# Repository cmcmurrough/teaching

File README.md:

teaching
========

Repository containing files related to CSE curriculum

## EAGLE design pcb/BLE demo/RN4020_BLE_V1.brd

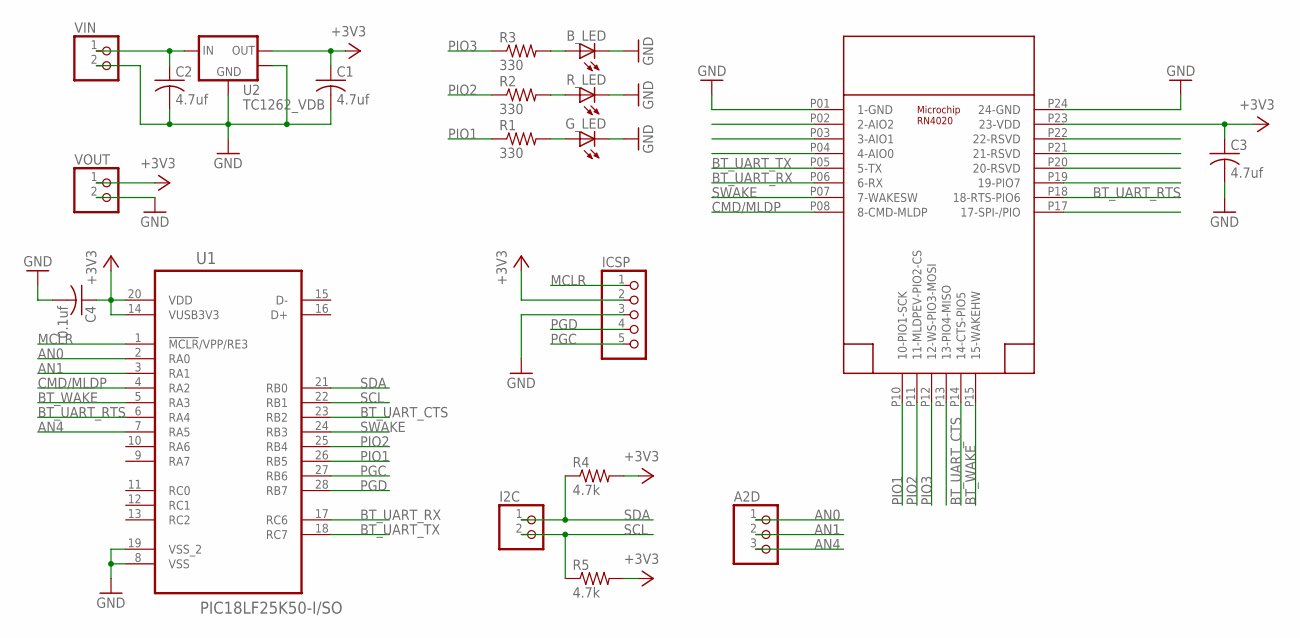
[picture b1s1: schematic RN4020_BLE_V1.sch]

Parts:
A2D: PINHD-1X3; 1X03
B_LED: LEDSMT1206; 1206
C1, C2, C3: 4.7uf; C1206
C4: 0.1uf; C1206
G_LED: LEDSMT1206; 1206
I2C: PINHD-1X2; 1X02
ICSP: PINHD-1X5; 1X05
R1, R2, R3: 330; R1206
R4, R5: 4.7k; R1206
R_LED: LEDSMT1206; 1206
U1: PIC18LF25K50-I/SO; SOIC127P1032X265-28N
U2: TC1262_VDB; SOT-223-3
U$1: RN4020; RN4020SMD
VIN: PINHD-1X2; 1X02
VOUT: PINHD-1X2; 1X02

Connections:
+3V3: C1.1, C3.1, C4.1, ICSP.2, R4.2, R5.2, U1.14 (VUSB3V3), U1.20 (VDD), U2.3 (VOUT), U$1.P23 (23-VDD), VOUT.1
AN0: A2D.1, U1.2 (RA0)
AN1: A2D.2, U1.3 (RA1)
AN4: A2D.3, U1.7 (RA5)
BT_UART_CTS: U1.23 (RB2), U$1.P14 (14-CTS-PIO5)
BT_UART_RTS: U1.6 (RA4), U$1.P18 (18-RTS-PIO6)
BT_UART_RX: U1.17 (RC6), U$1.P06 (6-RX)
BT_UART_TX: U1.18 (RC7), U$1.P05 (5-TX)
BT_WAKE: U1.5 (RA3), U$1.P15 (15-WAKEHW)
CMD/MLDP: U1.4 (RA2), U$1.P08 (8-CMD-MLDP)
GND: B_LED.C, C1.2, C2.2, C3.2, C4.2, G_LED.C, ICSP.3, R_LED.C, U1.8 (VSS), U1.19 (VSS_2), U2.2 (GND), U2.4 (TAB), U$1.P01 (1-GND), U$1.P24 (24-GND), VIN.2, VOUT.2
MCLR: ICSP.1, U1.1 (!MCLR!/VPP/RE3)
unnamed: G_LED.A, R1.2
unnamed: R2.2, R_LED.A
unnamed: B_LED.A, R3.2
unnamed: C2.1, U2.1 (VIN), VIN.1
PGC: ICSP.5, U1.27 (RB6)
PGD: ICSP.4, U1.28 (RB7)
PIO1: R1.1, U1.26 (RB5), U$1.P10 (10-PIO1-SCK)
PIO2: R2.1, U1.25 (RB4), U$1.P11 (11-MLDPEV-PIO2-CS)
PIO3: R3.1, U$1.P12 (12-WS-PIO3-MOSI)
SCL: I2C.2, R5.1, U1.22 (RB1)
SDA: I2C.1, R4.1, U1.21 (RB0)
SWAKE: U1.24 (RB3), U$1.P07 (7-WAKESW)

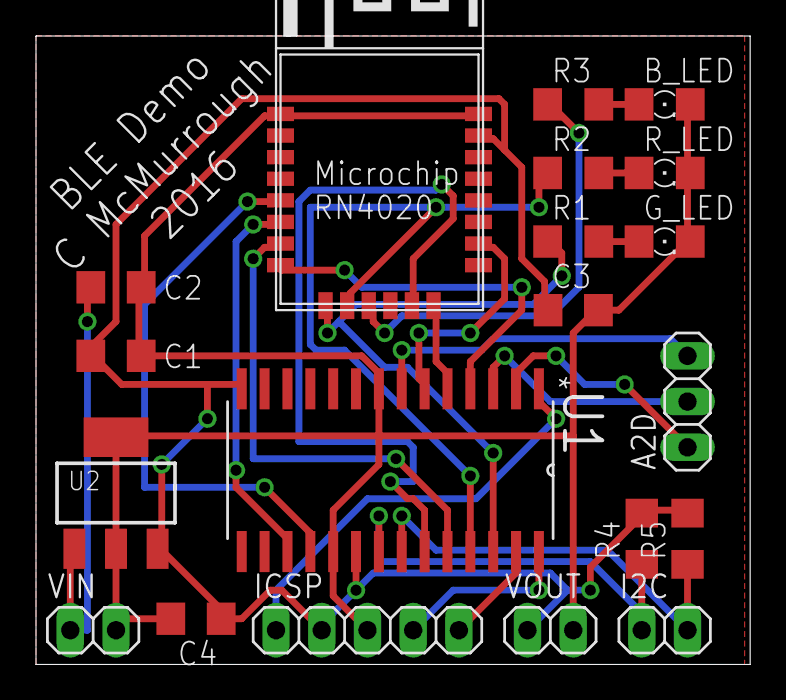
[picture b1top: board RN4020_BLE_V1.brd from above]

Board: 2 copper layers, 39.7 x 34.9 mm, 20 parts (0 on the bottom side), 24 nets.

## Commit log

2014-11-21 Added Teensy serial communication example
2015-02-11 Added OpenCV camera capture example
2015-02-11 Update CMakeLists.txt for windows compatability
2015-02-11 minor indentation fix
2015-02-11 minor indendation fix
2015-02-16 replaced <stdio.h> header include with <cstdio>
2015-02-17 Added OpenCV color labeling example
2015-02-17 changed display rectangle size
2015-02-19 Updated Teensy USB communication example for Teensy 3.1
2015-02-20 Added pcl_demo project
2015-02-20 replaced tabs with spaces
2015-02-26 Added Teensy servo control example
2015-03-03 Added Teensy stepper control demo
2015-04-28 Added raspi directory
2015-04-28 added -j4 instruction for multicore make
2015-07-07 Minor correction to comments
2015-07-18 updated build, removed manual actions
2015-07-21 added hello_world.s
2015-07-21 change to comments
2015-07-21 changed header comment
2015-07-21 changed comments
2015-07-21 renamed directory
2015-07-21 directory renaming
2015-07-23 added procedure call example
2015-07-23 fixed bug
2015-07-23 bug fix
2015-07-23 fixed procedure call bug
2015-07-23 update procedure call
2015-07-23 added procedure_call_parameters.s
2015-07-23 added printf example
2015-07-23 updated printf example
2015-07-25 updated printf with pop/push
2015-07-25 fixed exit bug in printf.s
2015-07-25 added scanf example
2015-07-25 fixed scanf.s error
2015-07-28 formatting
2015-07-28 fixed printing error
2015-07-28 Added compare_char example
2015-07-28 added warning message
2015-07-29 fixed comparison bug
2015-07-29 added recursive factorial example
2015-08-02 added mod example
2015-08-02 fixed mod example
2015-08-04 added debug example
2015-08-04 fixed formatting
2015-08-04 updated formatting flags
2015-08-04 fixed prints
2015-08-05 added accelstepper example
2015-08-05 added accelstepper project to teensy demo solution file
2015-08-12 updated accelstepper demo
2015-08-15 added exam_template.s
2015-10-07 added latex project charter example
2015-10-07 added document guides
2015-10-19 Added zmq OpenCV transmission demo
2015-10-19 updated zmq demo names
2015-10-19 updated cmakelinsts
2015-10-21 changed hello world
2015-10-21 reverted hello world change
2015-10-24 add SRS latex template
2015-11-07 temp commit for testing
2015-11-09 removed assembly examples
2015-11-18 added ADS latex template
2015-12-17 fixed type
2015-12-27 updated examples for OpenCV 3.x
2015-12-27 linux compatability
2015-12-28 portability improvements
2015-12-28 test
2015-12-28 bug fixes, completed linux compatability
2015-12-30 deleted dlls
2016-02-01 Updated ADS, added DDS documents
2016-02-01 minor exit bug fix, comment reformatting
2016-02-09 Updated project charter template
2016-02-09 updated charter outline
2016-02-15 fixed mismatched parenthesis
2016-03-07 added teensy HBridge demo
2016-03-12 updated doxygen tags
2016-06-21 added polling thread demo
2016-07-14 added SRS pdf
2016-07-15 added nodejs example
2016-07-16 minor change to output
2016-07-16 updated server.js
2016-09-19 updated nodejs examples
2016-09-20 minor edits to demo code
2016-10-31 added BLE demo PCB v1
2016-10-31 fixed BLE PCB, removed version from file name
2016-11-09 tabs to spaces
2016-12-13 added cmake fix
2017-02-04 added requestImage example
2017-04-19 added linker error fix
2017-10-23 deleted ADS guide
2017-10-23 deleted DDS guide
2017-10-23 deleted SRS guide
2017-11-16 updated PCL example
2018-01-25 updated placeholder image
2018-01-25 updated requirements worksheet
2018-02-06 added pupil tracker demo
2018-02-19 added individual sprint report
2018-05-14 update to template
2018-07-06 added iHSS57 closed loop stepper control example
2018-09-10 update to project charter template
2018-10-03 updated SRS
2018-11-11 update for OpenCV 4+ compatability
